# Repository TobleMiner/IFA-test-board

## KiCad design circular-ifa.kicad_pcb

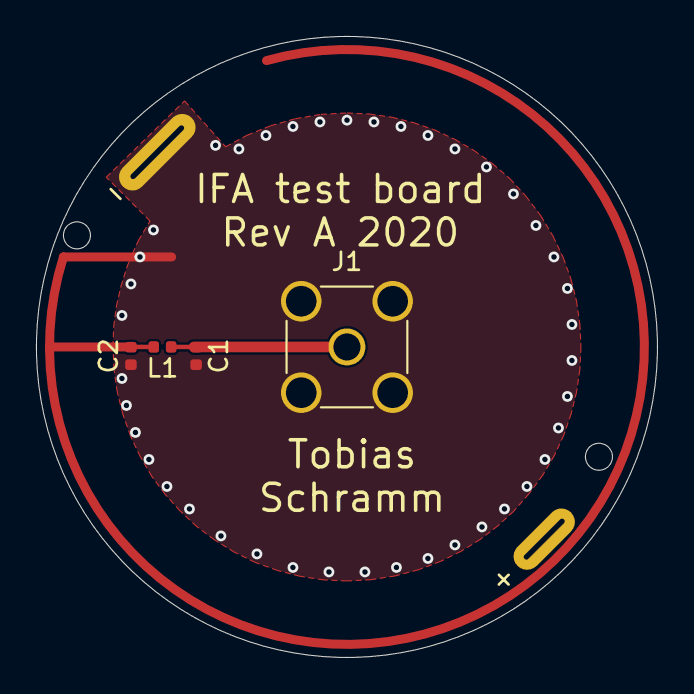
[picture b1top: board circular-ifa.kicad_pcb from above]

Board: 2 copper layers, 34.5 x 34.5 mm, 7 parts (1 on the bottom side), 3 nets.

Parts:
BT1: Battery_Cell; LIR3032_Panasonic_short
C1, C2: C; C_0402_1005Metric
H1, H2: MountingHole; MountingHole_1.5mm
J1: Conn_Coaxial; SMA_Amphenol_901-144_Vertical
L1: L; L_0402_1005Metric

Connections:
GND: BT1.2, C1.2, C2.2, J1.2
unnamed: C2.1, L1.2
unnamed: C1.1, J1.1, L1.1
